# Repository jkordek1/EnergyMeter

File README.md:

# EnergyMeter

## This project is still WIP

## About
Device for measuring power and energy consumption of AC load.
 
## Project status
- [x] Schematic
- [x] PCB
- [ ] First prototype fabricated
- [ ] Coding
- [ ] Enclosure design
- [ ] 3D CAD assembly and renders

## Main features
- Based on popular ESP-12 microcontroller
- HLW8032 energy meter IC

## BOM
BOM is available for download in BOM folder, all components are from LCSC.com.

 ## Images

## Project folder structure
    .
    ├── ...
    ├── Images                  # Images of the project
    ├── KiCADFiles              # Main folder
    │   ├── 3D models           # 3d models of components
    │   ├── BOM                 # Bill of Materials files
    │   ├── production          # gerber output folder
    │   └── Schematic.pdf       # Project schematic
    └── ...

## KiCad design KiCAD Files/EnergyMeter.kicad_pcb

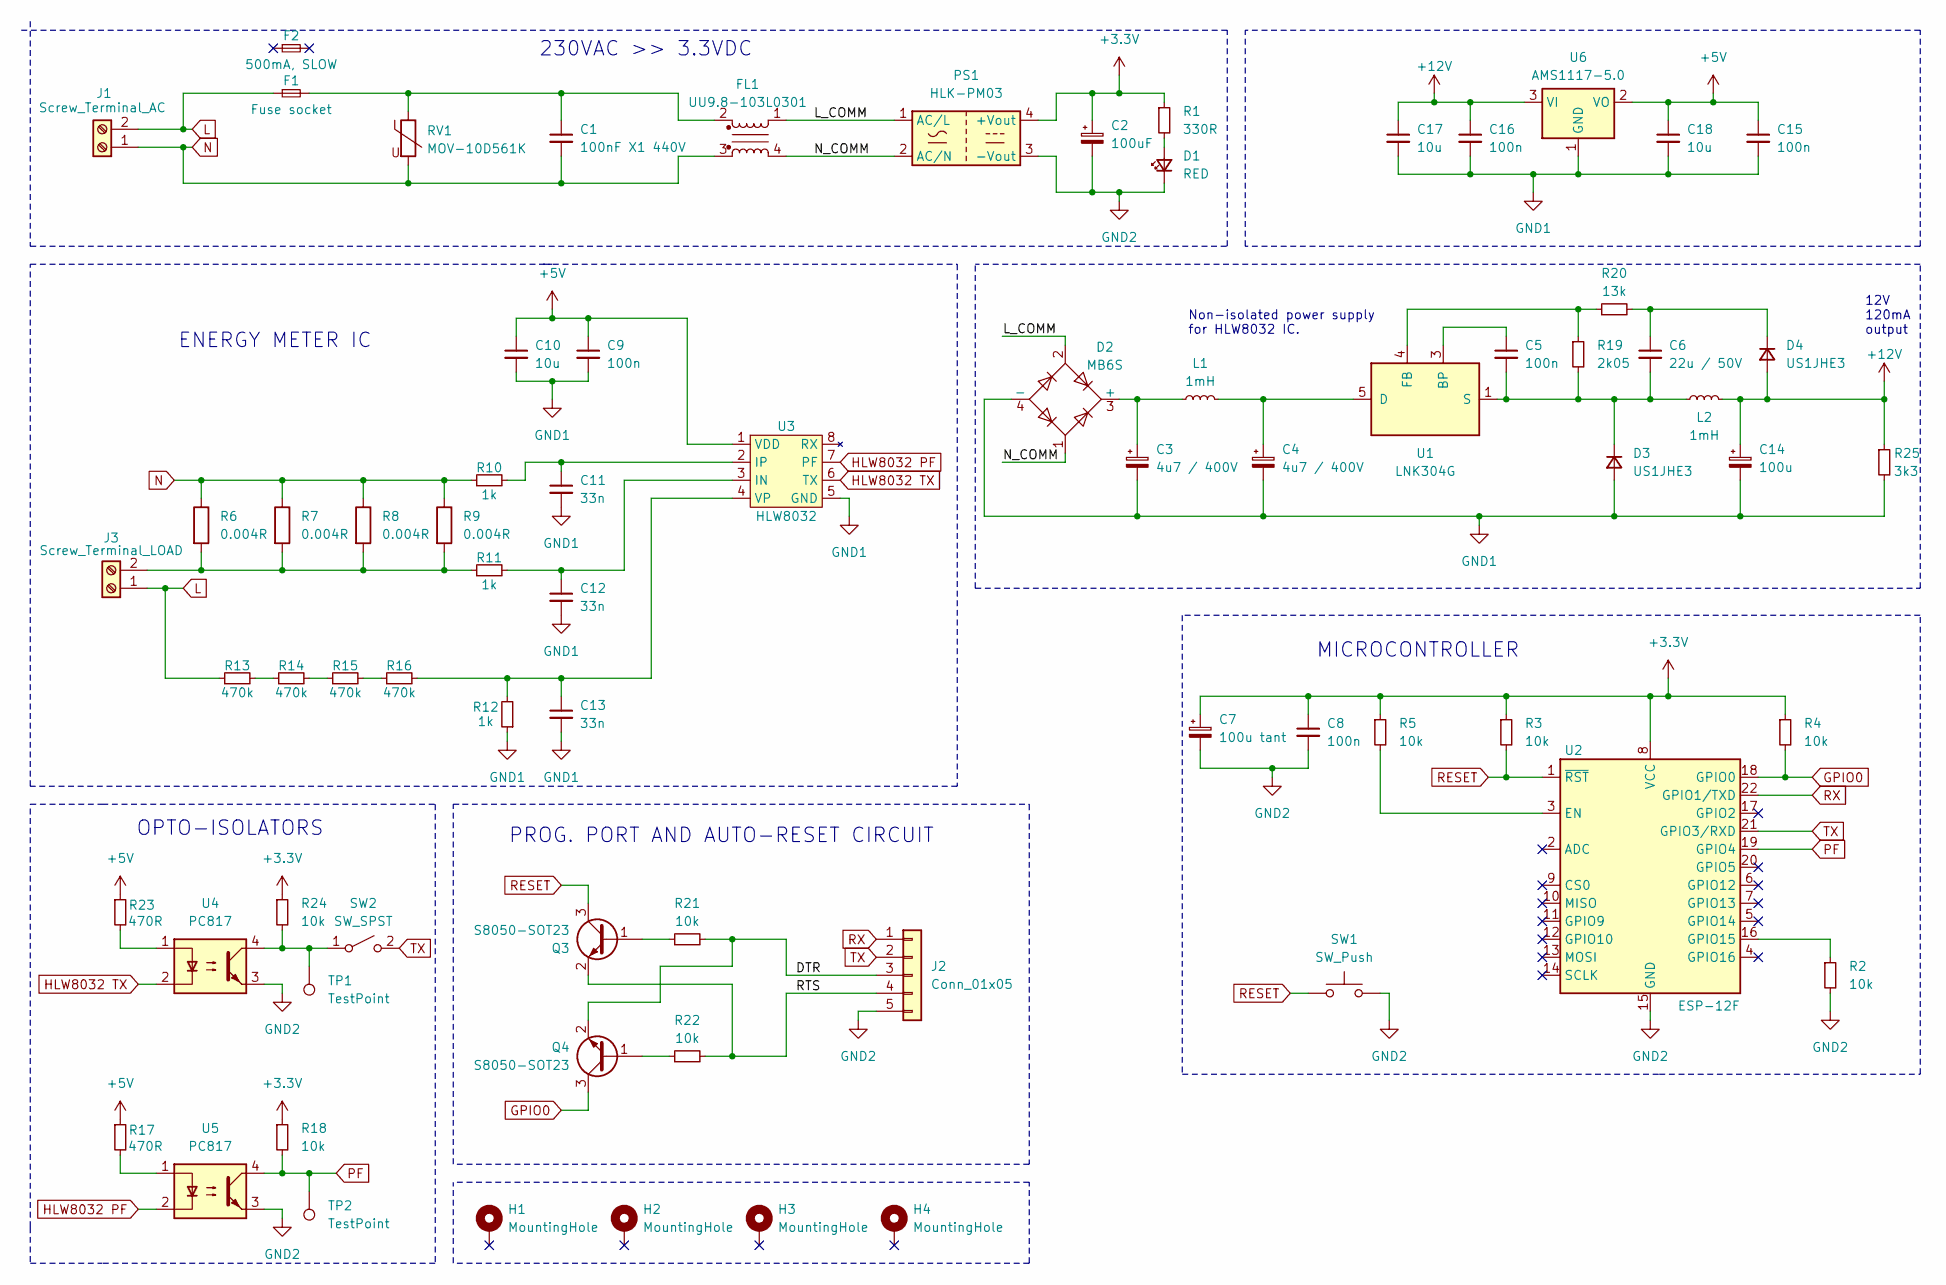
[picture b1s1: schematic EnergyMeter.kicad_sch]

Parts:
C1: 100nF X1 440V; C_Rect_L18.0mm_W8.0mm_P15.00mm_FKS3_FKP3; LCSC Part # C93321
C2: 100uF; CP_Radial_D8.0mm_P3.50mm; LCSC Part # C1594696
C3, C4: 4u7 / 400V; CP_Elec_8x10; LCSC Part # C250872
C5, C8, C9, C15, C16: 100n; C_0805_2012Metric; LCSC Part # C599848
C6: 22u / 50V; C_2220_5750Metric_Pad1.97x5.40mm_HandSolder; LCSC Part # C784103
C7: 100u tant; CP_EIA-7343-15_Kemet-W; LCSC Part # C110548
C10, C17, C18: 10u; C_1206_3216Metric; LCSC Part # C2174822
C11, C12, C13: 33n; C_0805_2012Metric; LCSC Part # C129656
C14: 100u; C_Elec_10x10.2; LCSC Part # C5158069
D1: RED; LED_0805_2012Metric; LCSC Part # C5879378
D2: MB6S; TO-269AA; LCSC Part # C114014
D3, D4: US1JHE3; D_SMA; LCSC Part # C142585
F1: Fuse socket; FH1-200CK-G; LCSC Part # C268204
F2: 500mA, SLOW; LCSC Part # C142727
FL1: UU9.8-103L0301; YDUU9.8-103L0301; LCSC Part # C5174477
H1, H2, H3, H4: MountingHole; MountingHole_3.2mm_M3_Pad_TopBottom
J1: Screw_Terminal_AC; KF7.62-2P; LCSC Part # C707824
J2: Conn_01x05; PinHeader_1x05_P2.54mm_Vertical; LCSC Part # C19190479
J3: Screw_Terminal_LOAD; KF7.62-2P; LCSC Part # C707824
L1, L2: 1mH; L_Taiyo-Yuden_NR-80xx_HandSoldering; LCSC Part # C19190456
PS1: HLK-PM03; Converter_ACDC_Hi-Link_HLK-PMxx; LCSC Part # C209904
Q3, Q4: S8050-SOT23; SOT-23; LCSC Part # C2891804
R1: 330R; R_0805_2012Metric; LCSC Part # C105877
R2, R3, R4, R5, R18, R21, R22, R24: 10k; R_0805_2012Metric; LCSC Part # C105877
R6, R7, R8, R9: 0.004R; R_2512_Shunt; LCSC Part # C375693
R10, R11, R12: 1k; R_0805_2012Metric; LCSC Part # C95781
R13, R14, R15, R16: 470k; R_0805_2012Metric; LCSC Part # C89104
R17, R23: 470R; R_0805_2012Metric; LCSC Part # C95781
R19: 2k05; R_0805_2012Metric; LCSC Part # C2091315
R20: 13k; R_0805_2012Metric; LCSC Part # C137592
R25: 3k3; R_0805_2012Metric; LCSC Part # C844842
RV1: MOV-10D561K; RV_Disc_D12mm_W3.9mm_P7.5mm; LCSC Part # C2656193
SW1: SW_Push; SW_Tactile_SPST_NO_Straight_CK_PTS636Sx25SMTRLFS; LCSC Part # C318938
SW2: SW_SPST; SW_DIP_SPSTx01_Slide_6.7x4.1mm_W6.73mm_P2.54mm_LowProfile_J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; LCSC Part # C54948
TP1, TP2: TestPoint; TestPoint_Pad_D3.0mm
U1: LNK304G; PowerIntegrations_SMD-8B; LCSC Part # C408815
U2: ESP-12F; ESP-12E; LCSC Part # C82891
U3: HLW8032; SOP-8_3.9x4.9mm_P1.27mm_custom; LCSC Part # C128023
U4, U5: PC817; DIP-4_W7.62mm; LCSC Part # C2833075
U6: AMS1117-5.0; SOT-223-3_TabPin2; LCSC Part # C22459281

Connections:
+3.3V: C2.1, C7.1, C8.1, PS1.4 (+Vout), R1.1, R3.1, R4.1, R5.1, R18.1, R24.1, U2.8 (VCC)
+5V: C9.1, C10.1, C15.1, C18.1, R17.1, R23.1, U3.1 (VDD), U6.2 (VO)
+12V: C14.1, C16.1, C17.1, D4.2 (A), L2.2, R25.1, U6.3 (VI)
/DTR: J2.3, Q4.2 (E), R21.2
/L_COMM: D2.2, FL1.1, PS1.1 (AC/L)
/N_COMM: D2.1, FL1.4, PS1.2 (AC/N)
/RTS: J2.4, Q3.2 (E), R22.2
GND1: C3.2, C4.2, C9.2, C10.2, C11.2, C12.2, C13.2, C14.2, C15.2, C16.2, C17.2, C18.2, D2.4 (-), D3.2 (A), R12.1, R25.2, U3.5 (GND), U6.1 (GND)
GND2: C2.2, C7.2, C8.2, D1.1 (K), J2.5, PS1.3 (-Vout), R2.2, SW1.2, U2.15 (GND), U4.3, U5.3
GPIO0: Q4.3 (C), R4.2, U2.18 (GPIO0)
HLW8032 PF: U3.7 (PF), U5.2
HLW8032 TX: U3.6 (TX), U4.2
L: F1.1, J1.2, J3.1, R13.1
N: C1.2, FL1.3, J1.1, R6.1, R7.1, R8.1, R9.1, R10.1, RV1.2
unnamed: C1.1, F1.2, FL1.2, RV1.1
unnamed: D1.2 (A), R1.2
unnamed: C3.1, D2.3 (+), L1.1
unnamed: C5.2, C6.2, D3.1 (K), L2.1, R19.2, U1.1 (S), U1.2 (S), U1.7 (S), U1.8 (S)
unnamed: C6.1, D4.1 (K), R20.2
unnamed: J3.2, R6.2, R7.2, R8.2, R9.2, R11.1
unnamed: Q3.1 (B), R21.1
unnamed: Q4.1 (B), R22.1
unnamed: R13.2, R14.1
unnamed: R14.2, R15.1
unnamed: R15.2, R16.1
unnamed: R17.2, U5.1
unnamed: R23.2, U4.1
unnamed: R24.2, SW2.1 (A), TP1.1, U4.4
unnamed: C5.1, U1.3 (BP)
unnamed: C4.1, L1.2, U1.5 (D)
unnamed: R19.1, R20.1, U1.4 (FB)
unnamed: R5.2, U2.3 (EN)
unnamed: R2.1, U2.16 (GPIO15)
unnamed: C12.1, R11.2, U3.3 (IN)
unnamed: C11.1, R10.2, U3.2 (IP)
unnamed: C13.1, R12.2, R16.2, U3.4 (VP)
PF: R18.2, TP2.1, U2.19 (GPIO4), U5.4
RESET: Q3.3 (C), R3.2, SW1.1, U2.1 (~RST)
RX: J2.1, U2.22 (GPIO1/TXD)
TX: J2.2, SW2.2 (B), U2.21 (GPIO3/RXD)

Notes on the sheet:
OPTO-ISOLATORS
ENERGY METER IC
12V 120mA output
230VAC >> 3.3VDC
MICROCONTROLLER
PROG. PORT AND AUTO-RESET CIRCUIT
Non-isolated power supply for HLW8032 IC.

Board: 2 copper layers, 72 parts (2 on the bottom side), 40 nets, no tracks yet.

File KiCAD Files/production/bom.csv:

Designator,Footprint,Quantity,Value,LCSC Part #
C1,C_Rect_L18.0mm_W8.0mm_P15.00mm_FKS3_FKP3,1,100nF X1 440V,C93321
"C10, C3, C5",1206,3,10u,C2174822
"C11, C12, C13",0805,3,33n,C129656
C2,CP_Radial_D8.0mm_P3.50mm,1,100u,C1594696
"C4, C6, C8, C9",0805,4,100n,C599848
C7,CP_EIA-7343-15_Kemet-W,1,100u tant,C110548
D1,0805,1,RED,C5879378
F1,FH1-200CK-G,1,Fuse socket,C268204
FL1,YDUU9.8-103L0301,1,UU9.8-103L0301,C5174477
J1,KF7.62-2P,1,Screw_Terminal_AC,C707824
J2,PinHeader_1x05_P2.54mm_Horizontal,1,Conn_01x05,C19190479
J3,KF7.62-2P,1,Screw_Terminal_LOAD,C707824
JP1,PinHeader_1x02_P2.54mm_Vertical,1,Jumper_2_Bridged,C706874
PS1,Converter_ACDC_Hi-Link_HLK-PMxx,1,HLK-PM01,C209903
"Q1, Q2",SOT-23,2,BSS138,C5250986
"Q3, Q4",SOT-23,2,S8050-SOT23,C2891804
R1,0805,1,330R,C105877
"R10, R11, R12",0805,3,1k,C95781
"R13, R14, R15, R16",0805,4,470k,C89104
"R17, R18, R19, R2, R20, R21, R22, R3, R4, R5",0805,10,10k,C105877
"R6, R7, R8, R9",R_2512_Shunt,4,0.004R,C375693
RV1,RV_Disc_D12mm_W3.9mm_P7.5mm,1,MOV-10D561K,C2656193
SW1,SW_Tactile_SPST_NO_Straight_CK_PTS636Sx25SMTRLFS,1,SW_Push,C318938
U1,SOT-223-3_TabPin2,1,AMS1117-3.3,C351784
U2,ESP-12E,1,ESP-12F,C82891
U3,SOP-8_3.9x4.9mm_P1.27mm_custom,1,HLW8032,C128023

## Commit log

2024-09-15 Repository created
2024-09-17 Schematic update
2024-09-17 TO-DO update
2024-09-19 Layout
2024-09-20 Remove backup folder
2024-09-24 pcb layout
2024-09-25 V1rev1
2024-09-26 3d model
